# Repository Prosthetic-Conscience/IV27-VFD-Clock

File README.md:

# IV27-VFD-Clock

This project uses an obscure Soviet era vacuum flourescent tube (IV27m). The intitial design idea was for a clock that looked like a scifi movie explosive device (think 80's cheesy movie bombs)

The first step was decoding the tube pinouts

These pins were decoded manually as the little extant documentation is in cyrillic for the most part

From there a main PCB and end cap PCBs were designed

The boards were spun using EaglePCB and built by JLPCB

From there assembly, feature expansion and done! It was modified to use an NTP time server, and uses the excellent WIFI manager arduino library. When the device boots and doesn't find a known SSID it rebootsd with a webserver running, and then scans for local SSIDs and then lets you select the correct one, load the password, and then if it connects successfully will reboot and connect itself.

Future plans for it involve using Geolocation to automatically set the timezone (versus the current hardcoded Central time) so it can be a bit more flexible.

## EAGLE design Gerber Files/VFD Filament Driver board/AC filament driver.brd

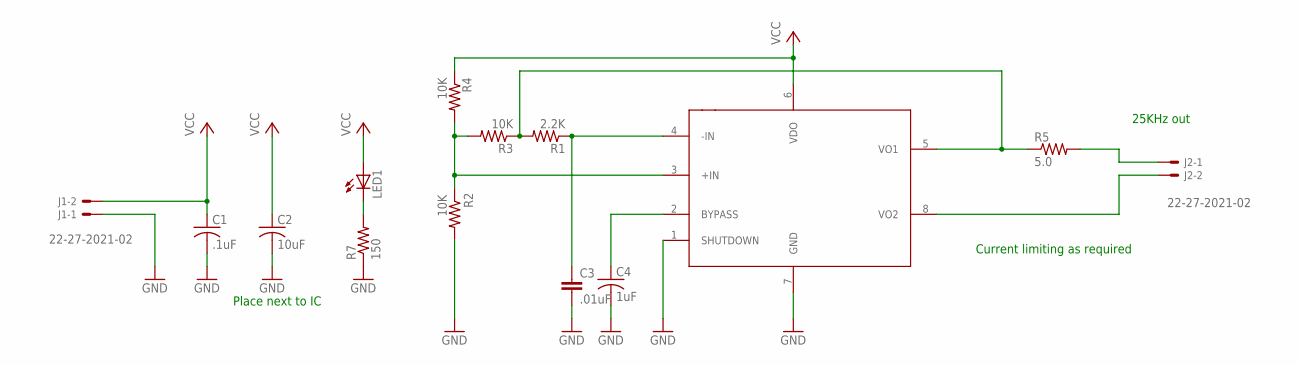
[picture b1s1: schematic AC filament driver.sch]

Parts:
C1: .1uF; C050-024X044
C2: 10uF; C025-060X050
C3: .01uF; C0805
C4: 1uF; C025-060X050
J1, J2: 22-27-2021-02; 6410-02
LED1: LEDCHIP-LED0805; CHIP-LED0805
R1: 2.2K; R0805
R2, R3, R4: 10K; R0805
R5: 5.0; R0805
R7: 150; R0805
U1: LM9022; SOIC127P600X175-8N

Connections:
GND: C1.2, C2.2, C3.2, C4.2, J1.1, R2.2, R7.1, U1.1 (SHUTDOWN), U1.7 (GND)
unnamed: LED1.C, R7.2
unnamed: R2.1, R3.2, R4.2, U1.3 (+IN)
unnamed: R1.2, R3.1, R5.1, U1.5 (VO1)
unnamed: C3.1, R1.1, U1.4 (-IN)
unnamed: C4.1, U1.2 (BYPASS)
unnamed: J2.1, R5.2
unnamed: J2.2, U1.8 (VO2)
VCC: C1.1, C2.1, J1.2, LED1.A, R4.1, U1.6 (VDO)

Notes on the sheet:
Current limiting as required
25KHz out
Place next to IC

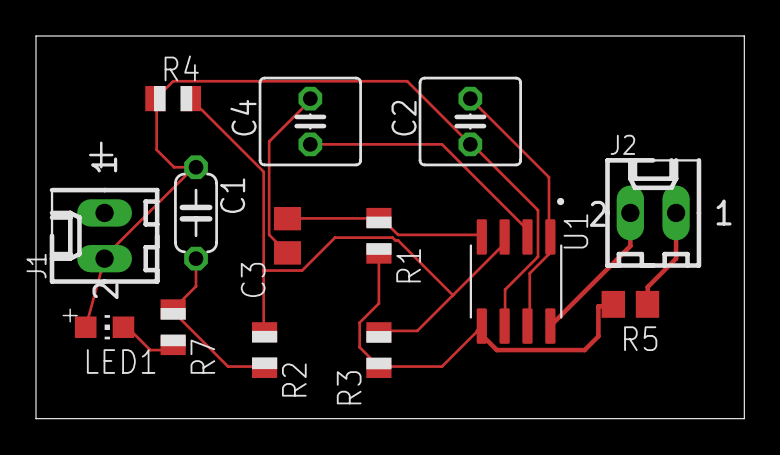
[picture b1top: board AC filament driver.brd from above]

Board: 2 copper layers, 39.4 x 21.3 mm, 14 parts (0 on the bottom side), 9 nets.

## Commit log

2022-09-09 Create stub
